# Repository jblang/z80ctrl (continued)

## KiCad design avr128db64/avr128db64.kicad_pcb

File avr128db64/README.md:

## z80ctrl with AVR128DB64

This is a experimental design for a new z80ctrl using the [AVR128DB64](https://www.microchip.com/en-us/product/avr128db64) microcontroller. 

**Important: This board has not been tested and is not yet complete.  Manufacture at your own risk.**

This part has several advantages over the current design using an ATmega1284P and I/O expander:

- Is a 64-pin part with more than enough I/O to interface with the RC2014 bus without any I/O expander. 
- Has configurable logic used to assert the wait signal on I/O requests without having to use an external NAND gate.
- Has multi-voltage I/O to interface the SD card directly without any level shifters.

The disadvantage is that it's a fine-pitched surface mount part, but since JLCPCB and PCBWay now offer board assembly service, it should be possible to get a fully assembled board from them.

### RAM

This board combines features of the previous through-hole z80ctrl board plus the RAM and RTC from the companion CPU/RAM/RTC board. The CPU is still on a separate board so that z80ctrl can be used with other CPUs.

The RAM uses the same bank switching scheme as the CPU/RAM/RTC board, with two 32K windows into 512K of RAM. The banks for the upper and lower window are stored in the upper and lower nybbles of a 74HCT574, respectively.  A 74HCT257 multiplexer selects between the two windows based on state of A15.  Bank switching on this board can be disabled via the slide switch, in which case A15 is connected directly to the SRAM and the output of the 74HCT257 is disabled.  A16-A18 are connected directly to the bus, so with bank switching disabled, a CPU with more address lines can be used. The AVR is connected to A16-A18 as well so it can work with all 512KB of RAM in either mode.

### RTC

The RTC used on the board is a [Microchip MCP2940N](https://www.microchip.com/en-us/product/mcp7940n) I2C RTC. The bus can be shared with additional I2C peripherals assuming they do not use the same address as the RTC.  

### Serial Buses

The 3-volt SPI, I2C, and UART signals are exposed on the [UEXT header](https://www.olimex.com/Products/Modules/UEXT/). The CS pin on the UEXT header is shared with the SD card, so the SD card must be removed if connecting an SPI device to the UEXT header.  Alternatively, if UART functionality is not needed, the 3-volt RX and TX pins can be used as alternate chip selects.

The 5V level-shifted I2C bus can optionally be exposed on USER6 and USER7 pins of the RC2014 bus (the same pins used for I2C by the SC126). Connecting and disconnecting the signals from the bus is controlled by a dip switch, which also allows connecting or disconnecting the RX, TX, RX2, and TX2 lines to the RC2014 bus. Unlike previous versions of z80ctrl, the SPI bus is no longer exposed on the RC2014 user pins.

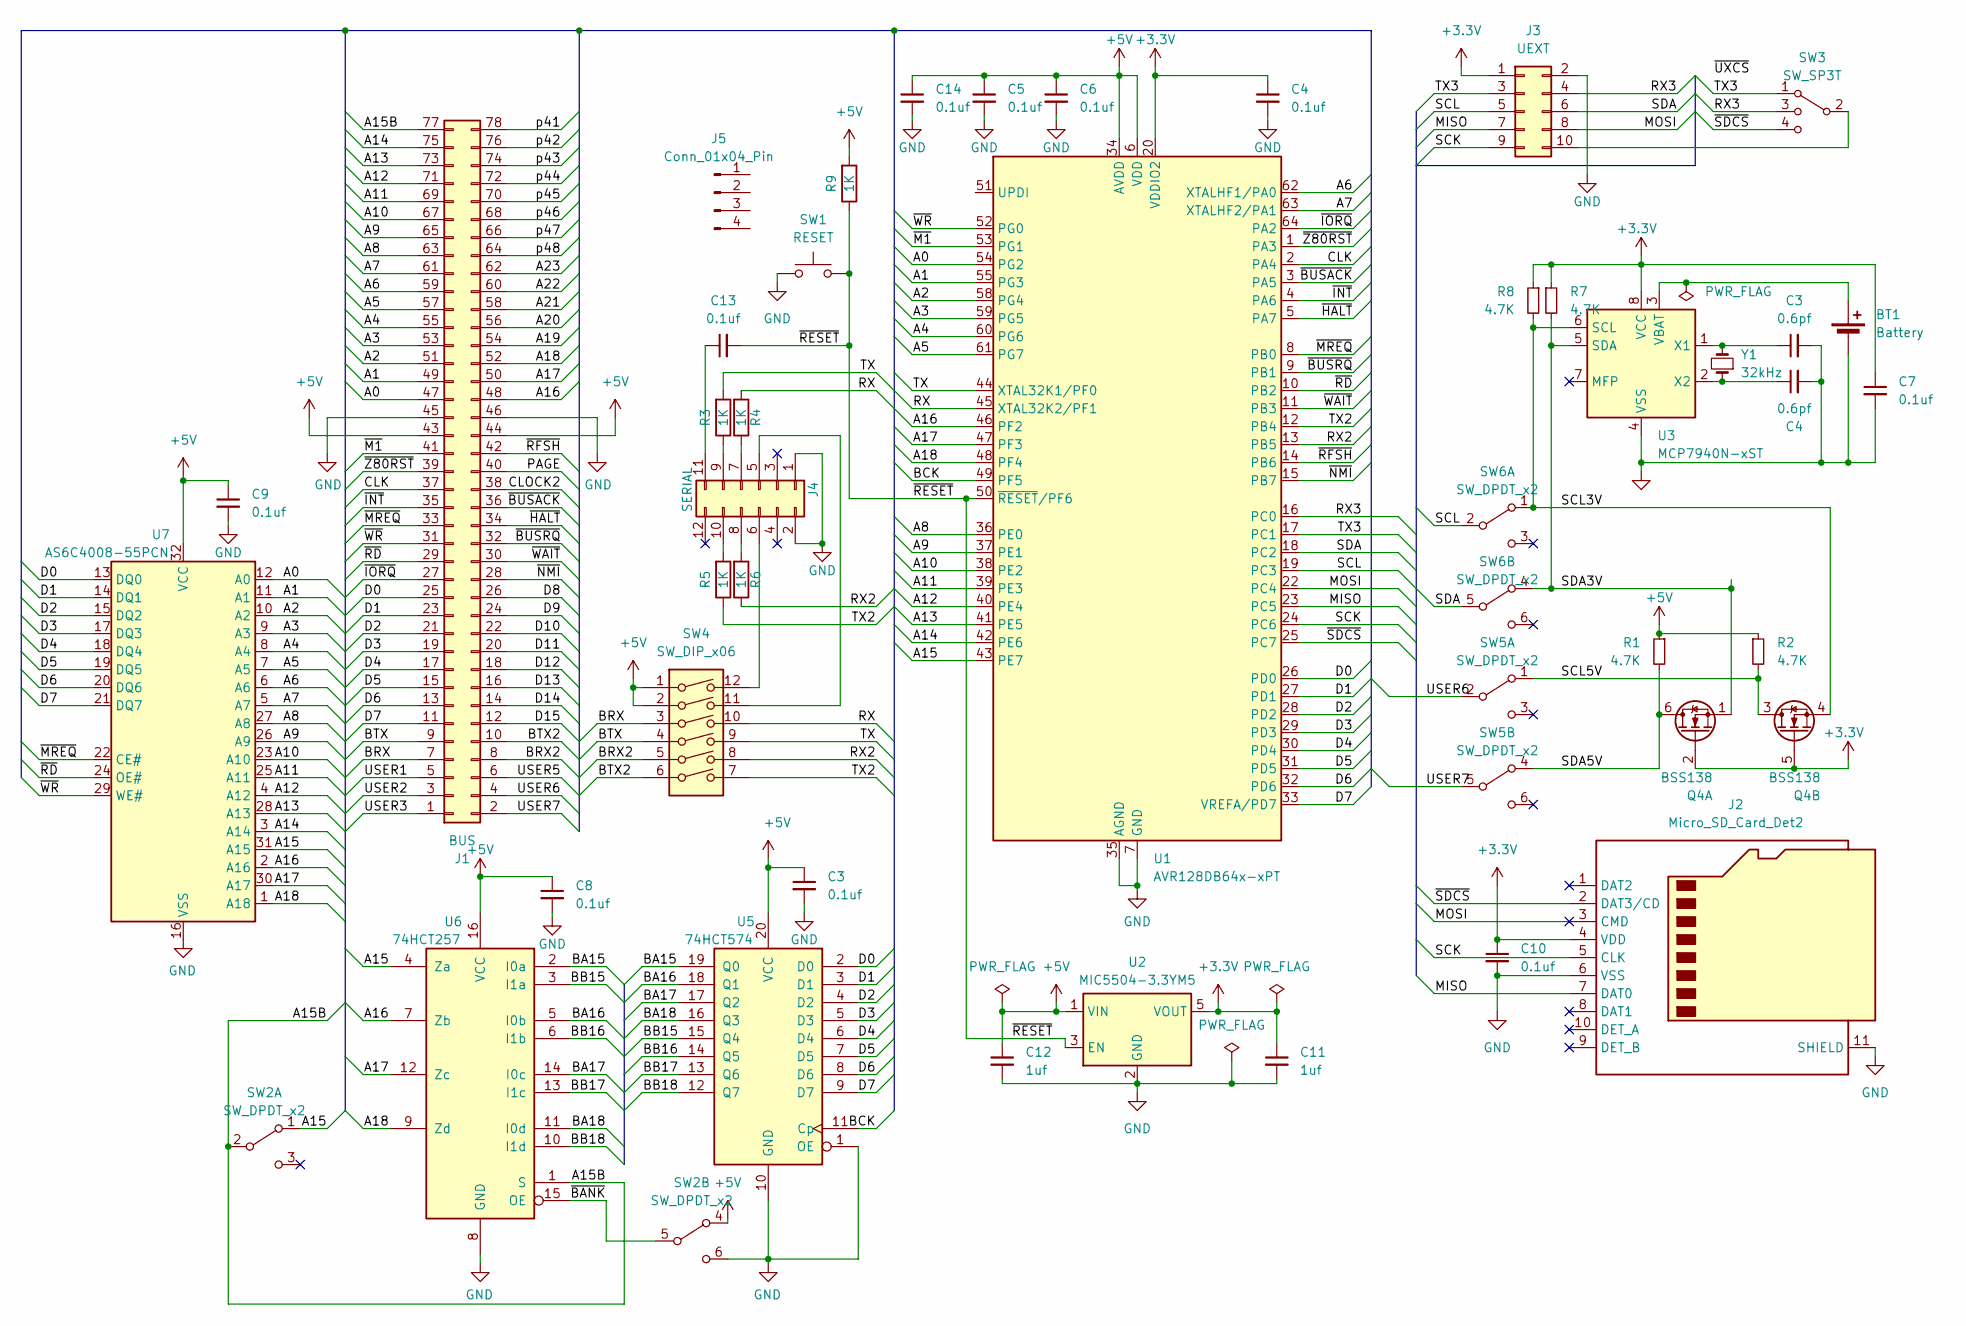
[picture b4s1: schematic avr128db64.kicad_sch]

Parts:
BT1: Battery; BatteryHolder_Keystone_3000_1x12mm
C3: 0.6pf; C_0402_1005Metric
C4, C5, C6, C7, C8, C9, C10, C13, C14: 0.1uf; C_0402_1005Metric
C11, C12: 1uf; C_0402_1005Metric
J1: BUS; PinHeader_2x39_P2.54mm_Horizontal
J2: Micro_SD_Card_Det2; microSD_HC_Molex_104031-0811
J3: UEXT; IDC-Header_2x05_P2.54mm_Vertical
J4: SERIAL; PinHeader_2x06_P2.54mm_Horizontal; MouserPN 649-1012938291204BLF; DigikeyPN PH2RA-12-UA
J5: Conn_01x04_Pin; PinHeader_1x04_P2.54mm_Horizontal
Q4: BSS138; SOT-363_SC-70-6
R1, R2, R7, R8: 4.7K; R_0402_1005Metric
R3, R4, R5, R6, R9: 1K; R_0402_1005Metric; MouserPN 603-CFR-25JB-1K0
SW1: RESET; SW_PUSH_6mm
SW2, SW5, SW6: SW_DPDT_x2; JS202011CQN
SW3: SW_SP3T; OS103011MS8QP1
SW4: SW_DIP_x06; SW_DIP_SPSTx06_Slide_9.78x17.42mm_W7.62mm_P2.54mm
U1: AVR128DB64x-xPT; TQFP-64_10x10mm_P0.5mm
U2: MIC5504-3.3YM5; SOT-23-5
U3: MCP7940N-xST; TSSOP-8_3x3mm_P0.65mm
U5: 74HCT574; DIP-20_W7.62mm; MouserPN 595-SN74HCT574N; DigikeyPN 296-1623-5-ND
U6: 74HCT257; DIP-16_W7.62mm; MouserPN 595-SN74HCT257N; DigikeyPN 296-8406-5-ND
U7: AS6C4008-55PCN; DIP-32_W15.24mm; MouserPN 913-AS6C4008-55PCN; DigikeyPN 1450-1027-ND
Y1: 32kHz; Crystal_SMD_3215-2Pin_3.2x1.5mm

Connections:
/A0: J1.47, U1.54 (PG2), U7.12 (A0)
/A1: J1.49, U1.55 (PG3), U7.11 (A1)
/A2: J1.51, U1.58 (PG4), U7.10 (A2)
/A3: J1.53, U1.59 (PG5), U7.9 (A3)
/A4: J1.55, U1.60 (PG6), U7.8 (A4)
/A5: J1.57, U1.61 (PG7), U7.7 (A5)
/A6: J1.59, U1.62 (XTALHF1/PA0), U7.6 (A6)
/A7: J1.61, U1.63 (XTALHF2/PA1), U7.5 (A7)
/A8: J1.63, U1.36 (PE0), U7.27 (A8)
/A9: J1.65, U1.37 (PE1), U7.26 (A9)
/A10: J1.67, U1.38 (PE2), U7.23 (A10)
/A11: J1.69, U1.39 (PE3), U7.25 (A11)
/A12: J1.71, U1.40 (PE4), U7.4 (A12)
/A13: J1.73, U1.41 (PE5), U7.28 (A13)
/A14: J1.75, U1.42 (PE6), U7.3 (A14)
/A15: SW2.1 (A), U1.43 (PE7), U6.4 (Za), U7.31 (A15)
/A15B: J1.77, SW2.2 (B), U6.1 (S)
/A16: J1.48, U1.46 (PF2), U6.7 (Zb), U7.2 (A16)
/A17: J1.50, U1.47 (PF3), U6.12 (Zc), U7.30 (A17)
/A18: J1.52, U1.48 (PF4), U6.9 (Zd), U7.1 (A18)
/A19: J1.54
/A20: J1.56
/A21: J1.58
/A22: J1.60
/A23: J1.62
/BA15: U5.19 (Q0), U6.2 (I0a)
/BA16: U5.18 (Q1), U6.5 (I0b)
/BA17: U5.17 (Q2), U6.14 (I0c)
/BA18: U5.16 (Q3), U6.11 (I0d)
/BB15: U5.15 (Q4), U6.3 (I1a)
/BB16: U5.14 (Q5), U6.6 (I1b)
/BB17: U5.13 (Q6), U6.13 (I1c)
/BB18: U5.12 (Q7), U6.10 (I1d)
/BCK: U1.49 (PF5), U5.11 (Cp)
/BRX: J1.7, SW4.3
/BRX2: J1.8, SW4.5
/BTX: J1.9, SW4.4
/BTX2: J1.10, SW4.6
/CLK: J1.37, U1.2 (PA4)
/CLOCK2: J1.38
/D0: J1.25, U1.26 (PD0), U5.2 (D0), U7.13 (DQ0)
/D1: J1.23, U1.27 (PD1), U5.3 (D1), U7.14 (DQ1)
/D2: J1.21, U1.28 (PD2), U5.4 (D2), U7.15 (DQ2)
/D3: J1.19, U1.29 (PD3), U5.5 (D3), U7.17 (DQ3)
/D4: J1.17, U1.30 (PD4), U5.6 (D4), U7.18 (DQ4)
/D5: J1.15, U1.31 (PD5), U5.7 (D5), U7.19 (DQ5)
/D6: J1.13, U1.32 (PD6), U5.8 (D6), U7.20 (DQ6)
/D7: J1.11, U1.33 (VREFA/PD7), U5.9 (D7), U7.21 (DQ7)
/D8: J1.26
/D9: J1.24
/D10: J1.22
/D11: J1.20
/D12: J1.18
/D13: J1.16
/D14: J1.14
/D15: J1.12
/MISO: J2.7 (DAT0), J3.7, U1.23 (PC5)
/MOSI: J2.3 (CMD), J3.8, U1.22 (PC4)
/PAGE: J1.40
/RX: R4.2, SW4.10, U1.45 (XTAL32K2/PF1)
/RX2: R6.1, SW4.8, U1.13 (PB5)
/RX3: J3.4, SW3.3, U1.16 (PC0)
/SCK: J2.5 (CLK), J3.9, U1.24 (PC6)
/SCL: J3.5, SW6.2 (B), U1.19 (PC3)
/SCL3V: R8.2, SW6.1 (A), U3.6 (SCL); also elsewhere on the board
/SCL5V: R2.2, SW5.1 (A); also elsewhere on the board
/SDA: J3.6, SW6.5 (B), U1.18 (PC2)
/SDA3V: R7.2, SW6.4 (A), U3.5 (SDA); also elsewhere on the board
/SDA5V: R1.2, SW5.4 (A); also elsewhere on the board
/TX: R3.2, SW4.9, U1.44 (XTAL32K1/PF0)
/TX2: R5.1, SW4.7, U1.12 (PB4)
/TX3: J3.3, SW3.1, U1.17 (PC1)
/USER1: J1.5
/USER2: J1.3
/USER3: J1.1
/USER5: J1.6
/USER6: J1.4, SW5.2 (B)
/USER7: J1.2, SW5.5 (B)
/p41: J1.78
/p42: J1.76
/p43: J1.74
/p44: J1.72
/p45: J1.70
/p46: J1.68
/p47: J1.66
/p48: J1.64
/~BANK: SW2.5 (B), U6.15 (OE)
/~BUSACK: J1.36, U1.3 (PA5)
/~BUSRQ: J1.32, U1.9 (PB1)
/~HALT: J1.34, U1.5 (PA7)
/~INT: J1.35, U1.4 (PA6)
/~IORQ: J1.27, U1.64 (PA2)
/~M1: J1.41, U1.53 (PG1)
/~MREQ: J1.33, U1.8 (PB0), U7.22 (CE#)
/~NMI: J1.28, U1.15 (PB7)
/~RD: J1.29, U1.10 (PB2), U7.24 (OE#)
/~RESET: C13.2, R9.1, SW1.2, U1.50 (~RESET/PF6), U2.3 (EN)
/~RFSH: J1.42, U1.14 (PB6)
/~SDCS: J2.2 (DAT3/CD), SW3.4, U1.25 (PC7)
/~WAIT: J1.30, U1.11 (PB3)
/~WR: J1.31, U1.52 (PG0), U7.29 (WE#)
/~Z80RST: J1.39, U1.1 (PA3)
GND: BT1.2 (-), C3.2, C4.2, C5.2, C6.2, C7.2, C8.2, C9.2, C10.2, C11.2, C12.2, C14.2, J1.45, J1.46, J2.6 (VSS), J2.11 (SHIELD), J3.2, J4.1, J4.2, SW1.1, SW2.6 (C), U1.7 (GND), U1.21 (GND), U1.35 (AGND), U1.57 (GND), U2.2 (GND), U3.4 (VSS), U5.1 (OE), U5.10 (GND), U6.8 (GND), U7.16 (VSS); also elsewhere on the board
unnamed: BT1.1 (+), U3.3 (VBAT)
unnamed: J3.10, SW3.2
unnamed: J4.5, SW4.11
unnamed: J4.6, SW4.12
unnamed: J4.7, R4.1
unnamed: J4.8, R6.2
unnamed: J4.9, R3.1
unnamed: J4.10, R5.2
unnamed: C13.1, J4.11

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
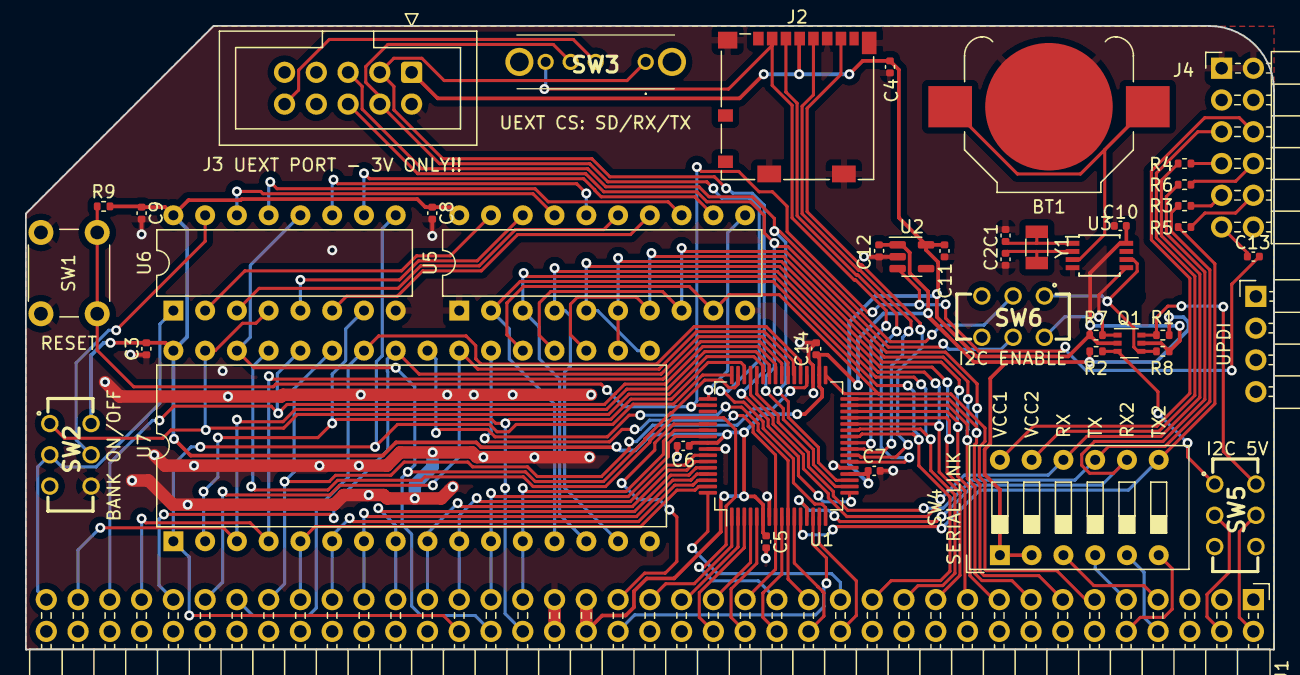
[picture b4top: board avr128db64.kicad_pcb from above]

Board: 2 copper layers, 99.8 x 49.9 mm, 43 parts (0 on the bottom side), 89 nets.

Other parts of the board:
C1, C2: 0.6pf; C_0402_1005Metric
Q1: BSS138; SOT-363_SC-70-6

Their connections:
/SCL3V: Q1.4 (S); also elsewhere on the board
/SCL5V: Q1.3 (D); also elsewhere on the board
/SDA3V: Q1.1 (S); also elsewhere on the board
/SDA5V: Q1.6 (D); also elsewhere on the board
GND: C1.2, C2.2; also elsewhere on the board

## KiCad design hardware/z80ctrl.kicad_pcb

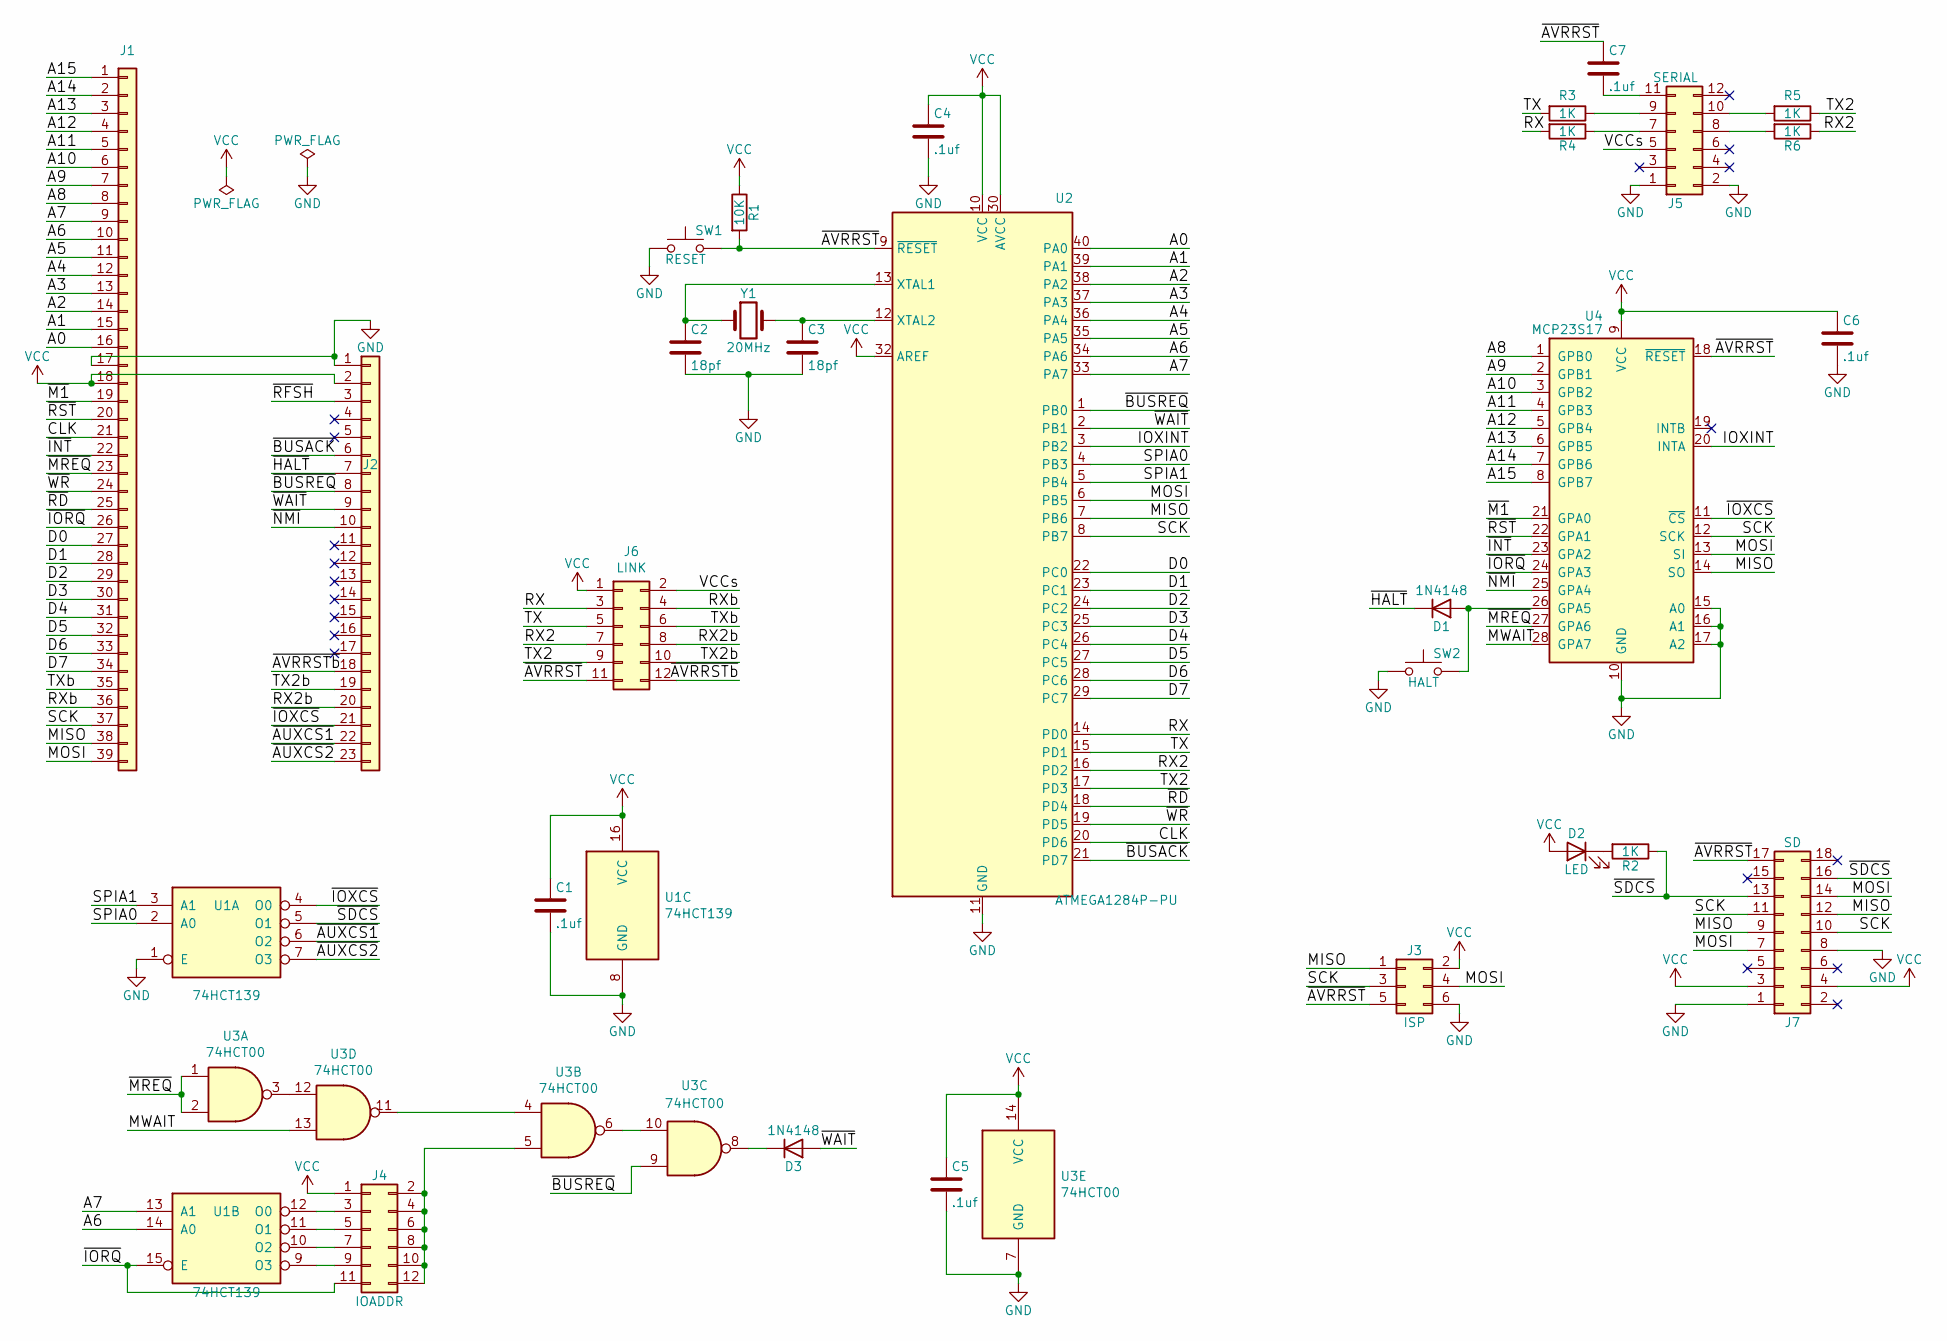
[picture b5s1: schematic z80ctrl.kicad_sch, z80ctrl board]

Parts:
C1, C4, C5, C6, C7: .1uf; C_Disc_D3.0mm_W1.6mm_P2.50mm; MouserPN 594-K104M15X7RF53L2; DigikeyPN BC5142-ND
C2: 18pf; C_Disc_D3.0mm_W1.6mm_P2.50mm; MouserPN 594-K180J15C0GF5TL2
C3: 18pf; C_Disc_D3.0mm_W1.6mm_P2.50mm; MouserPN 594-K180J15C0GF5TL2; DigikeyPN BC1004CT-ND
D1, D3: 1N4148; D_DO-35_SOD27_P7.62mm_Horizontal; MouserPN 512-1N4148; DigikeyPN 1N4148FS-ND
D2: LED; LED_D3.0mm; MouserPN 859-LTL2R3KGD-EM
J1: BUS; PinHeader_1x39_P2.54mm_Vertical; MouserPN 517-5121TG; DigikeyPN 2057-PH2RA-80-UA-ND
J2: BUSEXT; PinHeader_1x23_P2.54mm_Vertical; MouserPN 517-5121TG; DigikeyPN 2057-PH2RA-80-UA-ND
J3: ISP; PinHeader_2x03_P2.54mm_Vertical; MouserPN 710-61304011121; DigikeyPN S1012EC-40-ND
J4: IOADDR; PinHeader_2x06_P2.54mm_Vertical; MouserPN 710-61304011121; DigikeyPN S1012EC-40-ND
J5: SERIAL; PinHeader_2x06_P2.54mm_Horizontal; MouserPN 649-1012938291204BLF; DigikeyPN PH2RA-12-UA
J6: LINK; PinHeader_2x06_P2.54mm_Vertical; MouserPN 710-61304011121; DigikeyPN S1012EC-40-ND
J7: SD; PinHeader_2x09_P2.54mm_Vertical; MouserPN 485-254
R1: 10K; R_Axial_DIN0207_L6.3mm_D2.5mm_P7.62mm_Horizontal; MouserPN 603-CFR-25JB-52-10K; DigikeyPN 10KQBK-ND
R2, R3, R4, R5, R6: 1K; R_Axial_DIN0207_L6.3mm_D2.5mm_P7.62mm_Horizontal; MouserPN 603-CFR-25JB-1K0
SW1: RESET; SW_PUSH_6mm_H4.3mm; MouserPN 506-FSM4JH; DigikeyPN 450-1650-ND
SW2: HALT; SW_PUSH_6mm_H4.3mm; MouserPN 506-FSM4JH
U1: 74HCT139; DIP-16_W7.62mm_Socket; MouserPN 595-SN74HCT139N; DigikeyPN 296-8390-5-ND
U2: ATMEGA1284P-PU; DIP-40_W15.24mm_Socket; MouserPN 556-ATMEGA1284P-PU; DigikeyPN ATMEGA1284P-PU-ND
U3: 74HCT00; DIP-14_W7.62mm_Socket; MouserPN 595-SN74HCT00N; DigikeyPN 296-1603-5-ND
U4: MCP23S17; DIP-28_W7.62mm_Socket; MouserPN 579-MCP23S17-E/SP; DigikeyPN MCP23S17-E/SP-ND
Y1: 20MHz; Crystal_HC49-4H_Vertical; MouserPN 815-ABL-20-B2; DigikeyPN 535-9046-ND

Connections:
/A0: J1.16, U2.40 (PA0)
/A1: J1.15, U2.39 (PA1)
/A2: J1.14, U2.38 (PA2)
/A3: J1.13, U2.37 (PA3)
/A4: J1.12, U2.36 (PA4)
/A5: J1.11, U2.35 (PA5)
/A6: J1.10, U1.14 (A0), U2.34 (PA6)
/A7: J1.9, U1.13 (A1), U2.33 (PA7)
/A8: J1.8, U4.1 (GPB0)
/A9: J1.7, U4.2 (GPB1)
/A10: J1.6, U4.3 (GPB2)
/A11: J1.5, U4.4 (GPB3)
/A12: J1.4, U4.5 (GPB4)
/A13: J1.3, U4.6 (GPB5)
/A14: J1.2, U4.7 (GPB6)
/A15: J1.1, U4.8 (GPB7)
/CLK: J1.21, U2.20 (PD6)
/D0: J1.27, U2.22 (PC0)
/D1: J1.28, U2.23 (PC1)
/D2: J1.29, U2.24 (PC2)
/D3: J1.30, U2.25 (PC3)
/D4: J1.31, U2.26 (PC4)
/D5: J1.32, U2.27 (PC5)
/D6: J1.33, U2.28 (PC6)
/D7: J1.34, U2.29 (PC7)
/IOXINT: U2.3 (PB2), U4.20 (INTA)
/MISO: J1.38, J3.1, J7.9, J7.12, U2.7 (PB6), U4.14 (SO)
/MOSI: J1.39, J3.4, J7.7, J7.14, U2.6 (PB5), U4.13 (SI)
/MWAIT: U3.13, U4.28 (GPA7)
/RX: J6.3, R4.2, U2.14 (PD0)
/RX2: J6.7, R6.1, U2.16 (PD2)
/RX2b: J2.20, J6.8
/RXb: J1.36, J6.4
/SCK: J1.37, J3.3, J7.10, J7.11, U2.8 (PB7), U4.12 (SCK)
/SPIA0: U1.2 (A0), U2.4 (PB3)
/SPIA1: U1.3 (A1), U2.5 (PB4)
/TX: J6.5, R3.2, U2.15 (PD1)
/TX2: J6.9, R5.1, U2.17 (PD3)
/TX2b: J2.19, J6.10
/TXb: J1.35, J6.6
/VCCs: J5.5, J6.2
/~AUXCS1~: J2.22, U1.6 (O2)
/~AUXCS2~: J2.23, U1.7 (O3)
/~AVRRSTb~: J2.18, J6.12
/~AVRRST~: C7.1, J3.5, J6.11, J7.17, R1.2, SW1.2, U2.9 (~RESET), U4.18 (~RESET)
/~BUSACK~: J2.6, U2.21 (PD7)
/~BUSREQ~: J2.8, U2.1 (PB0), U3.9
/~HALT~: D1.1 (K), J2.7
/~INT~: J1.22, U4.23 (GPA2)
/~IORQ~: J1.26, J4.11, U1.15 (E), U4.24 (GPA3)
/~IOXCS~: J2.21, U1.4 (O0), U4.11 (~CS)
/~M1~: J1.19, U4.21 (GPA0)
/~MREQ~: J1.23, U3.1, U3.2, U4.27 (GPA6)
/~NMI~: J2.10, U4.25 (GPA4)
/~RD~: J1.25, U2.18 (PD4)
/~RST~: J1.20, U4.22 (GPA1)
/~SDCS~: J7.13, J7.16, R2.1, U1.5 (O1)
/~WAIT~: D3.2 (A), J2.9, U2.2 (PB1)
/~WR~: J1.24, U2.19 (PD5)
GND: C1.2, C2.2, C3.2, C4.2, C5.2, C6.2, J1.17, J2.1, J3.6, J5.1, J5.2, J7.1, J7.8, SW1.1, SW2.1, U1.1 (E), U1.8 (GND), U2.11 (GND), U2.31 (GND), U3.7 (GND), U4.10 (GND), U4.15 (A0), U4.16 (A1), U4.17 (A2)
unnamed: C2.1, U2.13 (XTAL1), Y1.1
unnamed: C3.1, U2.12 (XTAL2), Y1.2
unnamed: C7.2, J5.11
unnamed: D1.2 (A), SW2.2, U4.26 (GPA5)
unnamed: D2.1 (K), R2.2
unnamed: D3.1 (K), U3.8
unnamed: J4.3, U1.12 (O0)
unnamed: J4.5, U1.11 (O1)
unnamed: J4.7, U1.10 (O2)
unnamed: J4.9, U1.9 (O3)
unnamed: J4.2, J4.4, J4.6, J4.8, J4.10, J4.12, U3.5
unnamed: J5.7, R4.1
unnamed: J5.8, R6.2
unnamed: J5.9, R3.1
unnamed: J5.10, R5.2
unnamed: U3.6, U3.10
unnamed: U3.4, U3.11
unnamed: U3.3, U3.12
VCC: C1.1, C4.1, C5.1, C6.1, D2.2 (A), J1.18, J2.2, J3.2, J4.1, J6.1, J7.3, J7.4, R1.1, U1.16 (VCC), U2.10 (VCC), U2.30 (AVCC), U2.32 (AREF), U3.14 (VCC), U4.9 (VCC)

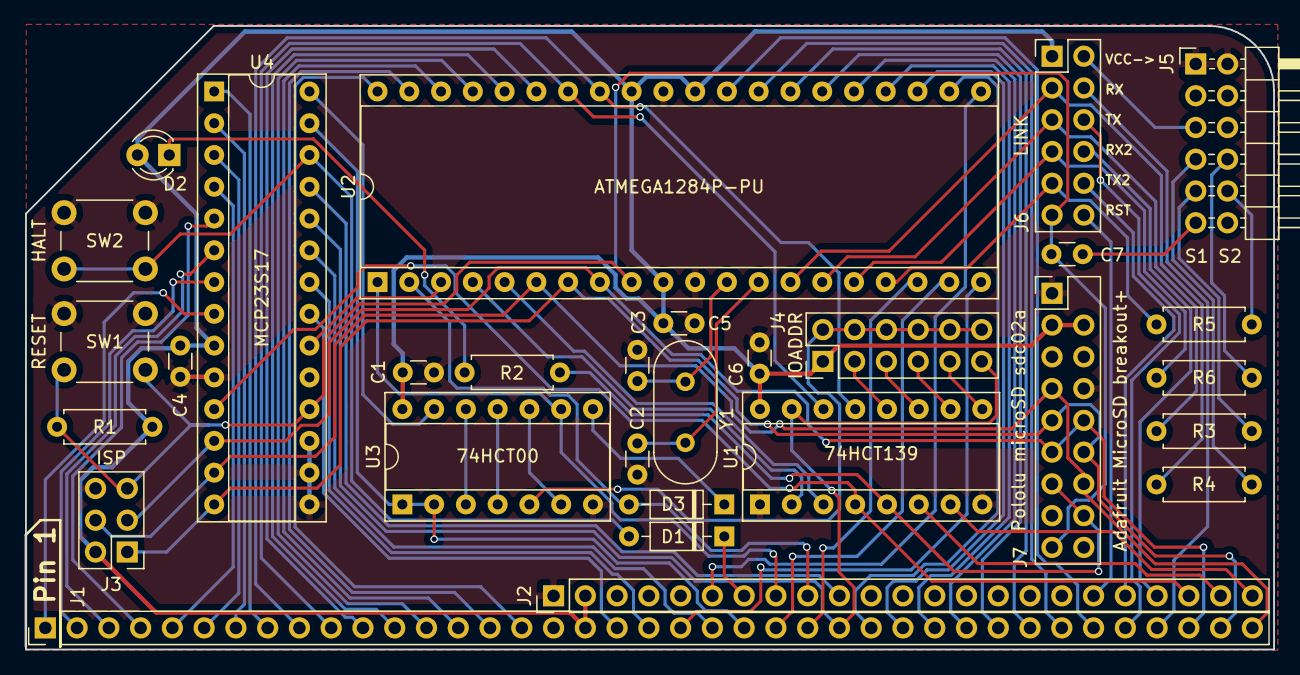
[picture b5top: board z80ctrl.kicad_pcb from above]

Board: 2 copper layers, 99.8 x 49.9 mm, 30 parts (0 on the bottom side), 79 nets.

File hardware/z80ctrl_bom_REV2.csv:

Component,Description,Part,References,Value,Footprint,Quantity Per PCB,Datasheet,MouserPN,DigikeyPN,TaydaPN,PololuPN
1,Unpolarized capacitor,C,C1 C4 C5 C6 C7,.1uf,C_Disc_D3.0mm_W1.6mm_P2.50mm,5,,594-K104K10X7RF5UL2,BC5228TB-ND,A-4008,
2,Unpolarized capacitor,C,C2 C3,18pf,C_Disc_D3.0mm_W1.6mm_P2.50mm,2,,594-K180J15C0GF5TL2,BC1004CT-ND,A-522,
3,Diode,D,D1 D3,1N4148,D_DO-35_SOD27_P7.62mm_Horizontal,2,,512-1N4148,1N4148FS-ND,A-157,
4,LED generic,LED,D2,LED,LED_D3.0mm,1,,,,A-1554,
5,,CONN_01X39,J1,BUS,Pin_Header_Straight_1x39_Pitch2.54mm,1,,,s1012ec-39-nd,A-638,
6,"Generic connector, single row, 01x23",Conn_01x23,J2,BUSEXT,Pin_Header_Straight_1x23_Pitch2.54mm,1,,,s1012ec-39-nd,A-638,
7,"Generic connector, double row, 02x06, odd/even pin numbering scheme (row 1 odd numbers, row 2 even numbers)",Conn_02x06_Odd_Even,J4,IOADDR,Pin_Header_Straight_2x06_Pitch2.54mm,1,,,952-2121-ND,A-197,
8,"Generic connector, double row, 02x03, odd/even pin numbering scheme (row 1 odd numbers, row 2 even numbers)",Conn_02x03_Odd_Even,J3,ISP,Pin_Header_Straight_2x03_Pitch2.54mm,1,,,,A-197,
9,"Generic connector, single row, 01x09",Conn_01x09,J7,SD,microSD_Breakout_VR_LS,1,https://www.pololu.com/product/2587,,,,2587
10,"Generic connector, single row, 01x06",Conn_01x06,J5,SERIAL1,Pin_Header_Angled_1x06_Pitch2.54mm,1,,,952-2372-ND,A-199,
11,"Generic connector, single row, 01x06",Conn_01x06,J6,SERIAL2,Pin_Header_Angled_1x06_Pitch2.54mm,1,,,952-2372-ND,A-199,
12,"Jumper, generic, normally closed",Jumper,JP1 JP2,Jumper,Pin_Header_Straight_1x02_Pitch2.54mm,2,,,952-2262-nd,A-197,
13,Resistor,R,R1,10K,R_Axial_DIN0207_L6.3mm_D2.5mm_P7.62mm_Horizontal,1,,CFR-25JB-52-10K,10KQBK-ND,A-2115,
14,Resistor,R,R2,1K,R_Axial_DIN0207_L6.3mm_D2.5mm_P7.62mm_Horizontal,1,,603-CFR-25JB-1K0,1.0KQBK-ND,A-2123,
15,"Push button switch, generic, two pins",SW_Push,SW2,HALT,SW_Tactile_Straight_KSA0Axx1LFTR,1,,,,A-197,
16,"Push button switch, generic, two pins",SW_Push,SW1,RESET,SW_Tactile_Straight_KSA0Axx1LFTR,1,,611-KSA0M412LFT,401-1814-ND,A-5127,
17,"Dual Decoder 1 of 4, Active low outputs",74LS139,U1,74HCT139,DIP-16_W7.62mm_Socket,1,,595-SN74HCT139N,296-8390-5-ND,,
18,"Dual D FlipFlop, Set & Reset",74HC74,U3,74HCT74,DIP-14_W7.62mm_Socket,1,74xx/74hc_hct74.pdf,595-SN74HCT74N,296-1625-5-ND,,
19,"PDIP40, 128k Flash, 16k SRAM, 4k EEPROM, JTAG",ATMEGA1284P-PU,U2,ATMEGA1284P-PU,DIP-40_W15.24mm_Socket,1,http://www.atmel.com/Images/Atmel-8272-8-bit-AVR-microcontro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,556-ATMEGA1284P-PU,ATMEGA1284P-PU-ND,,
20,16-Bit I/O Expander with SPI Interface (PDIP/SOIC/SSOP),MCP23S17,U4,MCP23S17,DIP-28_W7.62mm_Socket,1,http://ww1.microchip.com/downloads/en/DeviceDoc/20001952C.pdf,579-MCP23S17-E/SP,MCP23S17-E/SP-ND,,
21,Two pin crystal,Crystal,Y1,20MHz,Crystal_HC49-4H_Vertical,1,,815-ABL-20-B2,535-9046-ND,A-236,

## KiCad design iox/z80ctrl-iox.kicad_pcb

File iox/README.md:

[See Wiki](https://github.com/jblang/z80ctrl/wiki/IO-Expander-Board)

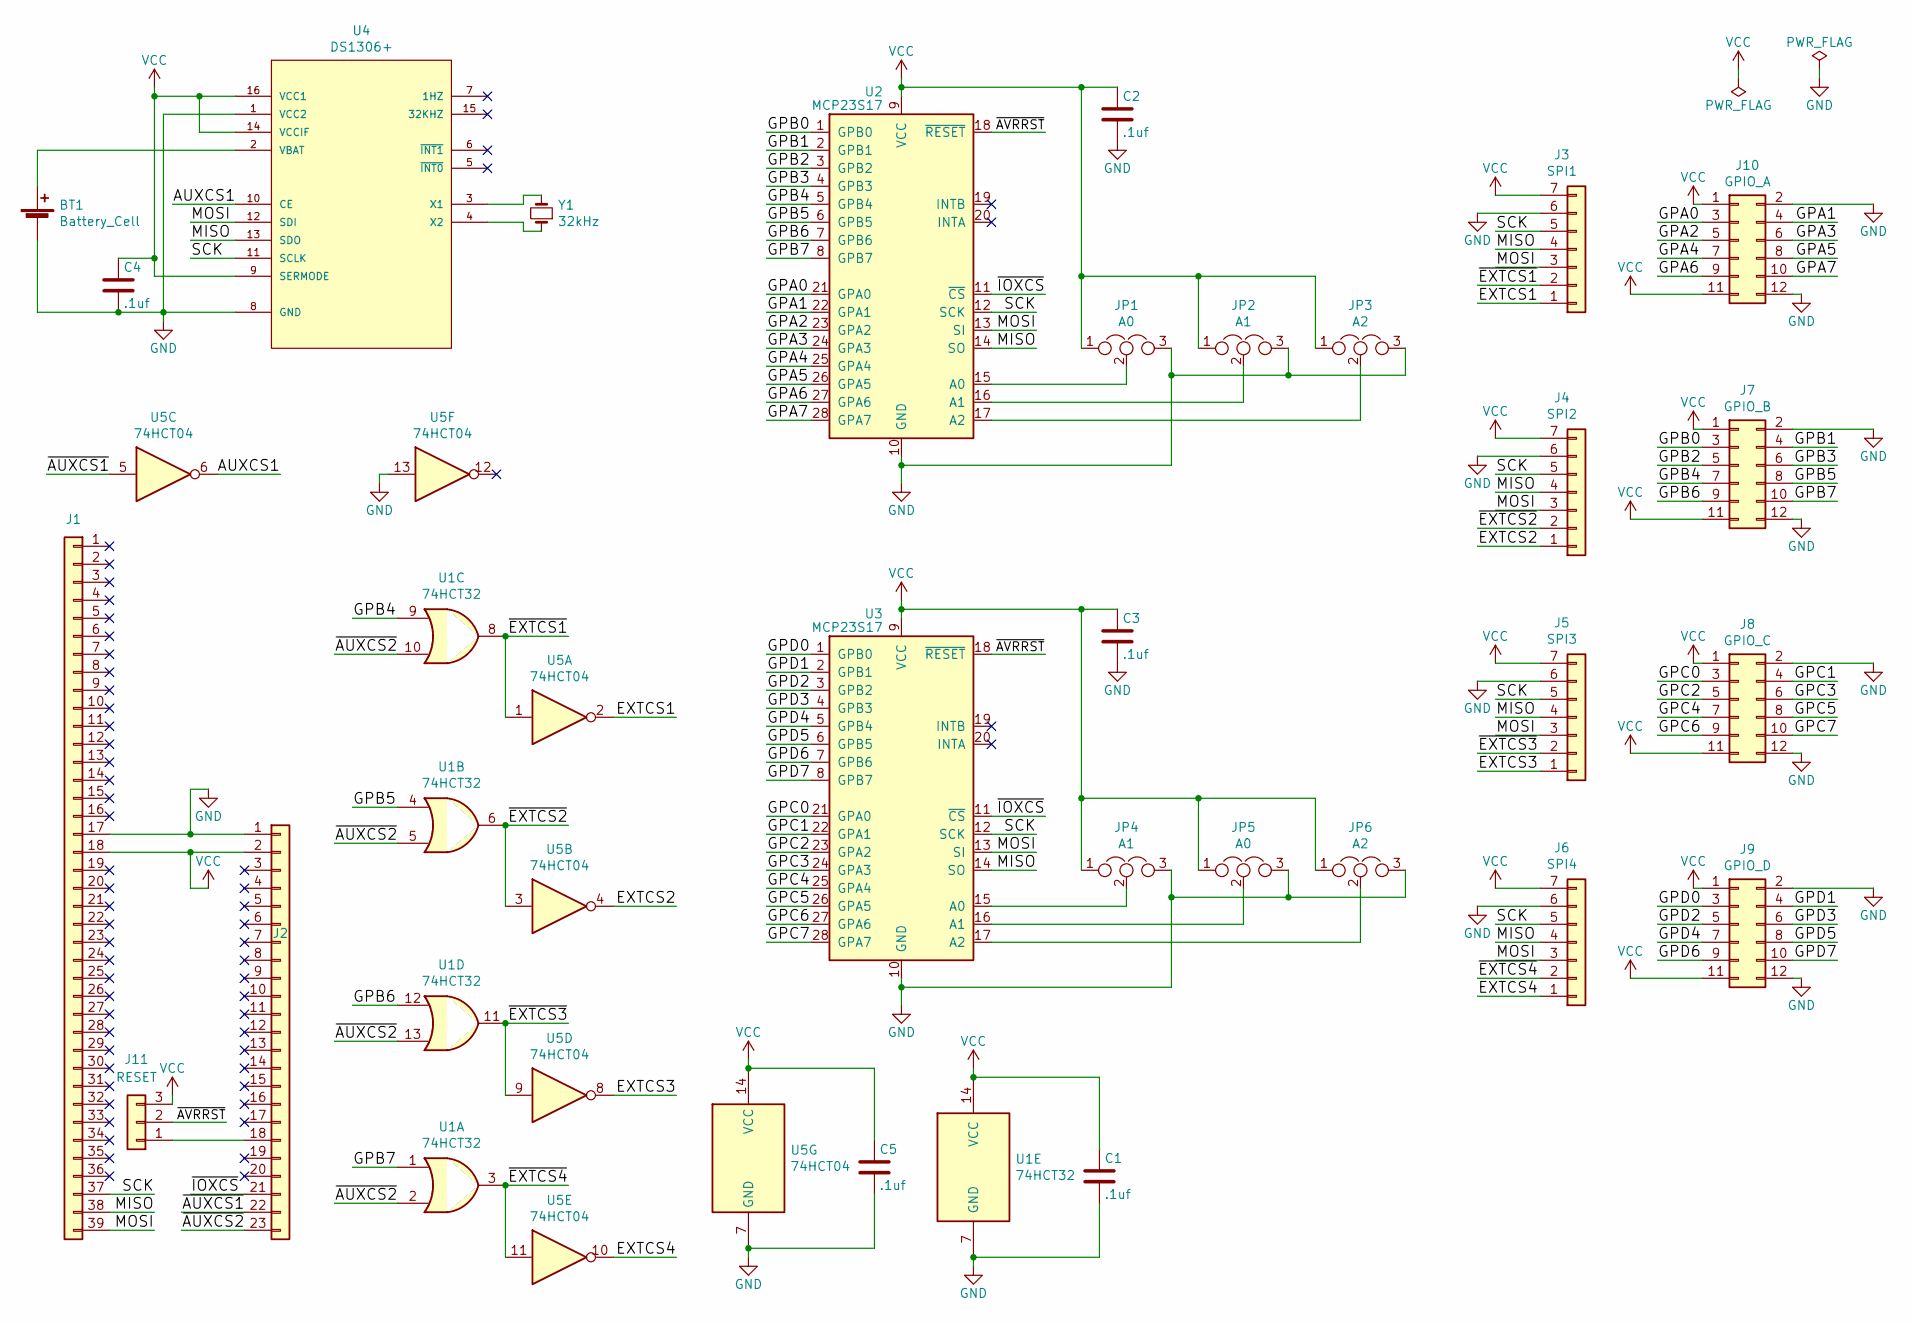
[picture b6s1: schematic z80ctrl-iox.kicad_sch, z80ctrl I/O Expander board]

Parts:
BT1: Battery_Cell; BatteryHolder_Keystone_3001_1x12mm
C1, C2, C3, C4, C5: .1uf; C_Disc_D3.0mm_W1.6mm_P2.50mm
J1: BUS; PinHeader_1x39_P2.54mm_Vertical; DigikeyPN s1012ec-39-nd
J2: BUSEXT; PinHeader_1x23_P2.54mm_Vertical; DigikeyPN s1012ec-39-nd
J3: SPI1; PinHeader_1x07_P2.54mm_Horizontal
J4: SPI2; PinHeader_1x07_P2.54mm_Horizontal
J5: SPI3; PinHeader_1x07_P2.54mm_Horizontal
J6: SPI4; PinHeader_1x07_P2.54mm_Horizontal
J7: GPIO_B; PinHeader_2x06_P2.54mm_Horizontal
J8: GPIO_C; PinHeader_2x06_P2.54mm_Horizontal
J9: GPIO_D; PinHeader_2x06_P2.54mm_Horizontal
J10: GPIO_A; PinHeader_2x06_P2.54mm_Horizontal
J11: RESET; PinHeader_1x03_P2.54mm_Vertical
JP1, JP5: A0; PinHeader_1x03_P2.54mm_Vertical
JP2, JP4: A1; PinHeader_1x03_P2.54mm_Vertical
JP3, JP6: A2; PinHeader_1x03_P2.54mm_Vertical
U1: 74HCT32; DIP-14_W7.62mm_Socket
U2, U3: MCP23S17; DIP-28_W7.62mm_Socket; MouserPN 579-MCP23S17-E/SP; DigikeyPN MCP23S17-E/SP-ND
U4: DS1306+; DIP-16_W7.62mm_Socket
U5: 74HCT04; DIP-14_W7.62mm_Socket
Y1: 32kHz; Crystal_DS26_D2.0mm_L6.0mm_Horizontal

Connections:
/AUXCS1: U4.10 (CE), U5.6
/EXTCS1: J3.1, U5.2
/EXTCS2: J4.1, U5.4
/EXTCS3: J5.1, U5.8
/EXTCS4: J6.1, U5.10
/GPA0: J10.3, U2.21 (GPA0)
/GPA1: J10.4, U2.22 (GPA1)
/GPA2: J10.5, U2.23 (GPA2)
/GPA3: J10.6, U2.24 (GPA3)
/GPA4: J10.7, U2.25 (GPA4)
/GPA5: J10.8, U2.26 (GPA5)
/GPA6: J10.9, U2.27 (GPA6)
/GPA7: J10.10, U2.28 (GPA7)
/GPB0: J7.3, U2.1 (GPB0)
/GPB1: J7.4, U2.2 (GPB1)
/GPB2: J7.5, U2.3 (GPB2)
/GPB3: J7.6, U2.4 (GPB3)
/GPB4: J7.7, U1.9, U2.5 (GPB4)
/GPB5: J7.8, U1.4, U2.6 (GPB5)
/GPB6: J7.9, U1.12, U2.7 (GPB6)
/GPB7: J7.10, U1.1, U2.8 (GPB7)
/GPC0: J8.3, U3.21 (GPA0)
/GPC1: J8.4, U3.22 (GPA1)
/GPC2: J8.5, U3.23 (GPA2)
/GPC3: J8.6, U3.24 (GPA3)
/GPC4: J8.7, U3.25 (GPA4)
/GPC5: J8.8, U3.26 (GPA5)
/GPC6: J8.9, U3.27 (GPA6)
/GPC7: J8.10, U3.28 (GPA7)
/GPD0: J9.3, U3.1 (GPB0)
/GPD1: J9.4, U3.2 (GPB1)
/GPD2: J9.5, U3.3 (GPB2)
/GPD3: J9.6, U3.4 (GPB3)
/GPD4: J9.7, U3.5 (GPB4)
/GPD5: J9.8, U3.6 (GPB5)
/GPD6: J9.9, U3.7 (GPB6)
/GPD7: J9.10, U3.8 (GPB7)
/MISO: J1.38, J3.4, J4.4, J5.4, J6.4, U2.14 (SO), U3.14 (SO), U4.13 (SDO)
/MOSI: J1.39, J3.3, J4.3, J5.3, J6.3, U2.13 (SI), U3.13 (SI), U4.12 (SDI)
/SCK: J1.37, J3.5, J4.5, J5.5, J6.5, U2.12 (SCK), U3.12 (SCK), U4.11 (SCLK)
/~AUXCS1~: J2.22, U5.5
/~AUXCS2~: J2.23, U1.2, U1.5, U1.10, U1.13
/~AVRRST~: J11.2, U2.18 (~RESET), U3.18 (~RESET)
/~EXTCS1~: J3.2, U1.8, U5.1
/~EXTCS2~: J4.2, U1.6, U5.3
/~EXTCS3~: J5.2, U1.11, U5.9
/~EXTCS4~: J6.2, U1.3, U5.11
/~IOXCS~: J2.21, U2.11 (~CS), U3.11 (~CS)
GND: BT1.2 (-), C1.2, C2.2, C3.2, C4.2, C5.2, J1.17, J2.1, J3.6, J4.6, J5.6, J6.6, J7.2, J7.12, J8.2, J8.12, J9.2, J9.12, J10.2, J10.12, JP1.3, JP2.3, JP3.3, JP4.3, JP5.3, JP6.3, U1.7 (GND), U2.10 (GND), U3.10 (GND), U4.1 (VCC2), U4.8 (GND), U5.7 (GND), U5.13
unnamed: BT1.1 (+), U4.2 (VBAT)
unnamed: J2.18, J11.1
unnamed: JP1.2, U2.15 (A0)
unnamed: JP2.2, U2.16 (A1)
unnamed: JP3.2, U2.17 (A2)
unnamed: JP4.2, U3.15 (A0)
unnamed: JP5.2, U3.16 (A1)
unnamed: JP6.2, U3.17 (A2)
unnamed: U4.3 (X1), Y1.2
unnamed: U4.4 (X2), Y1.1
VCC: C1.1, C2.1, C3.1, C4.1, C5.1, J1.18, J2.2, J3.7, J4.7, J5.7, J6.7, J7.1, J7.11, J8.1, J8.11, J9.1, J9.11, J10.1, J10.11, J11.3, JP1.1, JP2.1, JP3.1, JP4.1, JP5.1, JP6.1, U1.14 (VCC), U2.9 (VCC), U3.9 (VCC), U4.9 (SERMODE), U4.14 (VCCIF), U4.16 (VCC1), U5.14 (VCC)

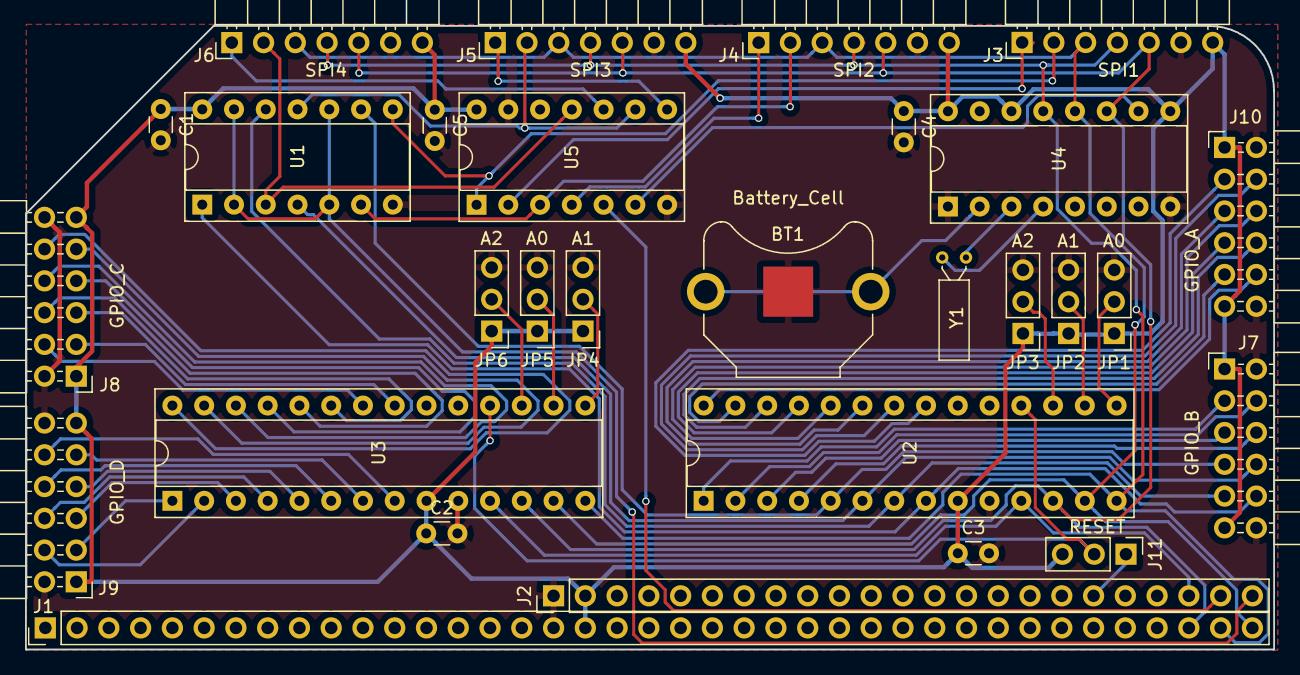
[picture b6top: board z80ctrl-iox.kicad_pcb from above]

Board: 2 copper layers, 99.8 x 49.9 mm, 29 parts (0 on the bottom side), 60 nets.
